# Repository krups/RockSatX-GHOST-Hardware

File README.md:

# RockSatX-GHOST-Hardware
PCB design files and documentation for the hardware used in the University of Kentucky's 2025 RockSat-XG KRUPS payload. Further information for each component is found in its respective folder.

### Hardware Folders
- [Capsule](Capsule)
- [FemtoSat](FemtoSat)
- [BaseStation/RocketStation](RocketStation)
- [LR62XE Adapter/Breakout](LR62XEAdapter)

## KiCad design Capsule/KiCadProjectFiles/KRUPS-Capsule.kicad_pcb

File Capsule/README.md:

# Capsule
PCB design files and documentation for the re-entry capsule used in the University of Kentucky's 2025 RockSat-XG KRUPS payload

### PCB Render

### Components
- [Raspberry Pi Pico 2 W (4MB Flash)](https://datasheets.raspberrypi.com/picow/pico-2-w-datasheet.pdf)
- [Fanstel LR62XE 1W 868/915MHz LoRa Modem](https://static1.squarespace.com/static/561459a2e4b0b39f5cefa12e/t/63ddc4b1dd728b424f1a6c23/1675478197953/LR62E_LR62XE_M262X840XE_Product+Specifications.pdf)
- [FSM300 9-Axis IMU](https://www.mouser.com/datasheet/2/1480/FSM30x_Datasheet-3196253.pdf)
- [H3LIS100DL 3-axis accelerometer](https://www.st.com/resource/en/datasheet/h3lis100dl.pdf)
- [MCP9600 thermocouple to digital converter](https://ww1.microchip.com/downloads/aemDocuments/documents/MSLD/ProductDocuments/DataSheets/MCP960X-L0X-RL0X-Thermocouple-EMF-to-Temperature-Converter-plus-minus-1-5-degrees-Celcius-Maximum-Accuracy-DS20005426.pdf)

### Pin Mapping
| Pico 2 GPIO Pin | Net Name |
| --- | --- |
| GPIO0 | T_IRIDIUM |
| GPIO1 | R_IRIDIUM |
| GPIO2 | SDA |
| GPIO3 | SCL |
| GPIO4 | TX1 |
| GPIO5 | RX1 |
| GPIO6 | TX_GPS |
| GPIO7 | RX_GPS |
| GPIO12 | SD_SPI_MISO |
| GPIO13 | SD_SPI_CS |
| GPIO14 | SD_SPI_CLK |
| GPIO15 | SD_SPI_MOSI |
| GPIO16 | LORA_SPI_MISO |
| GPIO17 | LORA_SPI_CSN |
| GPIO18 | LORA_SPI_CLK |
| GPIO19 | LORA_SPI_MOSI |
| GPIO20 | LORA_ANTW |
| GPIO21 | LORA_RESET |
| GPIO22 | LORA_BUSY |
| GPIO26 | LORA_DIO1 |
| GPIO27 | PWMLS |

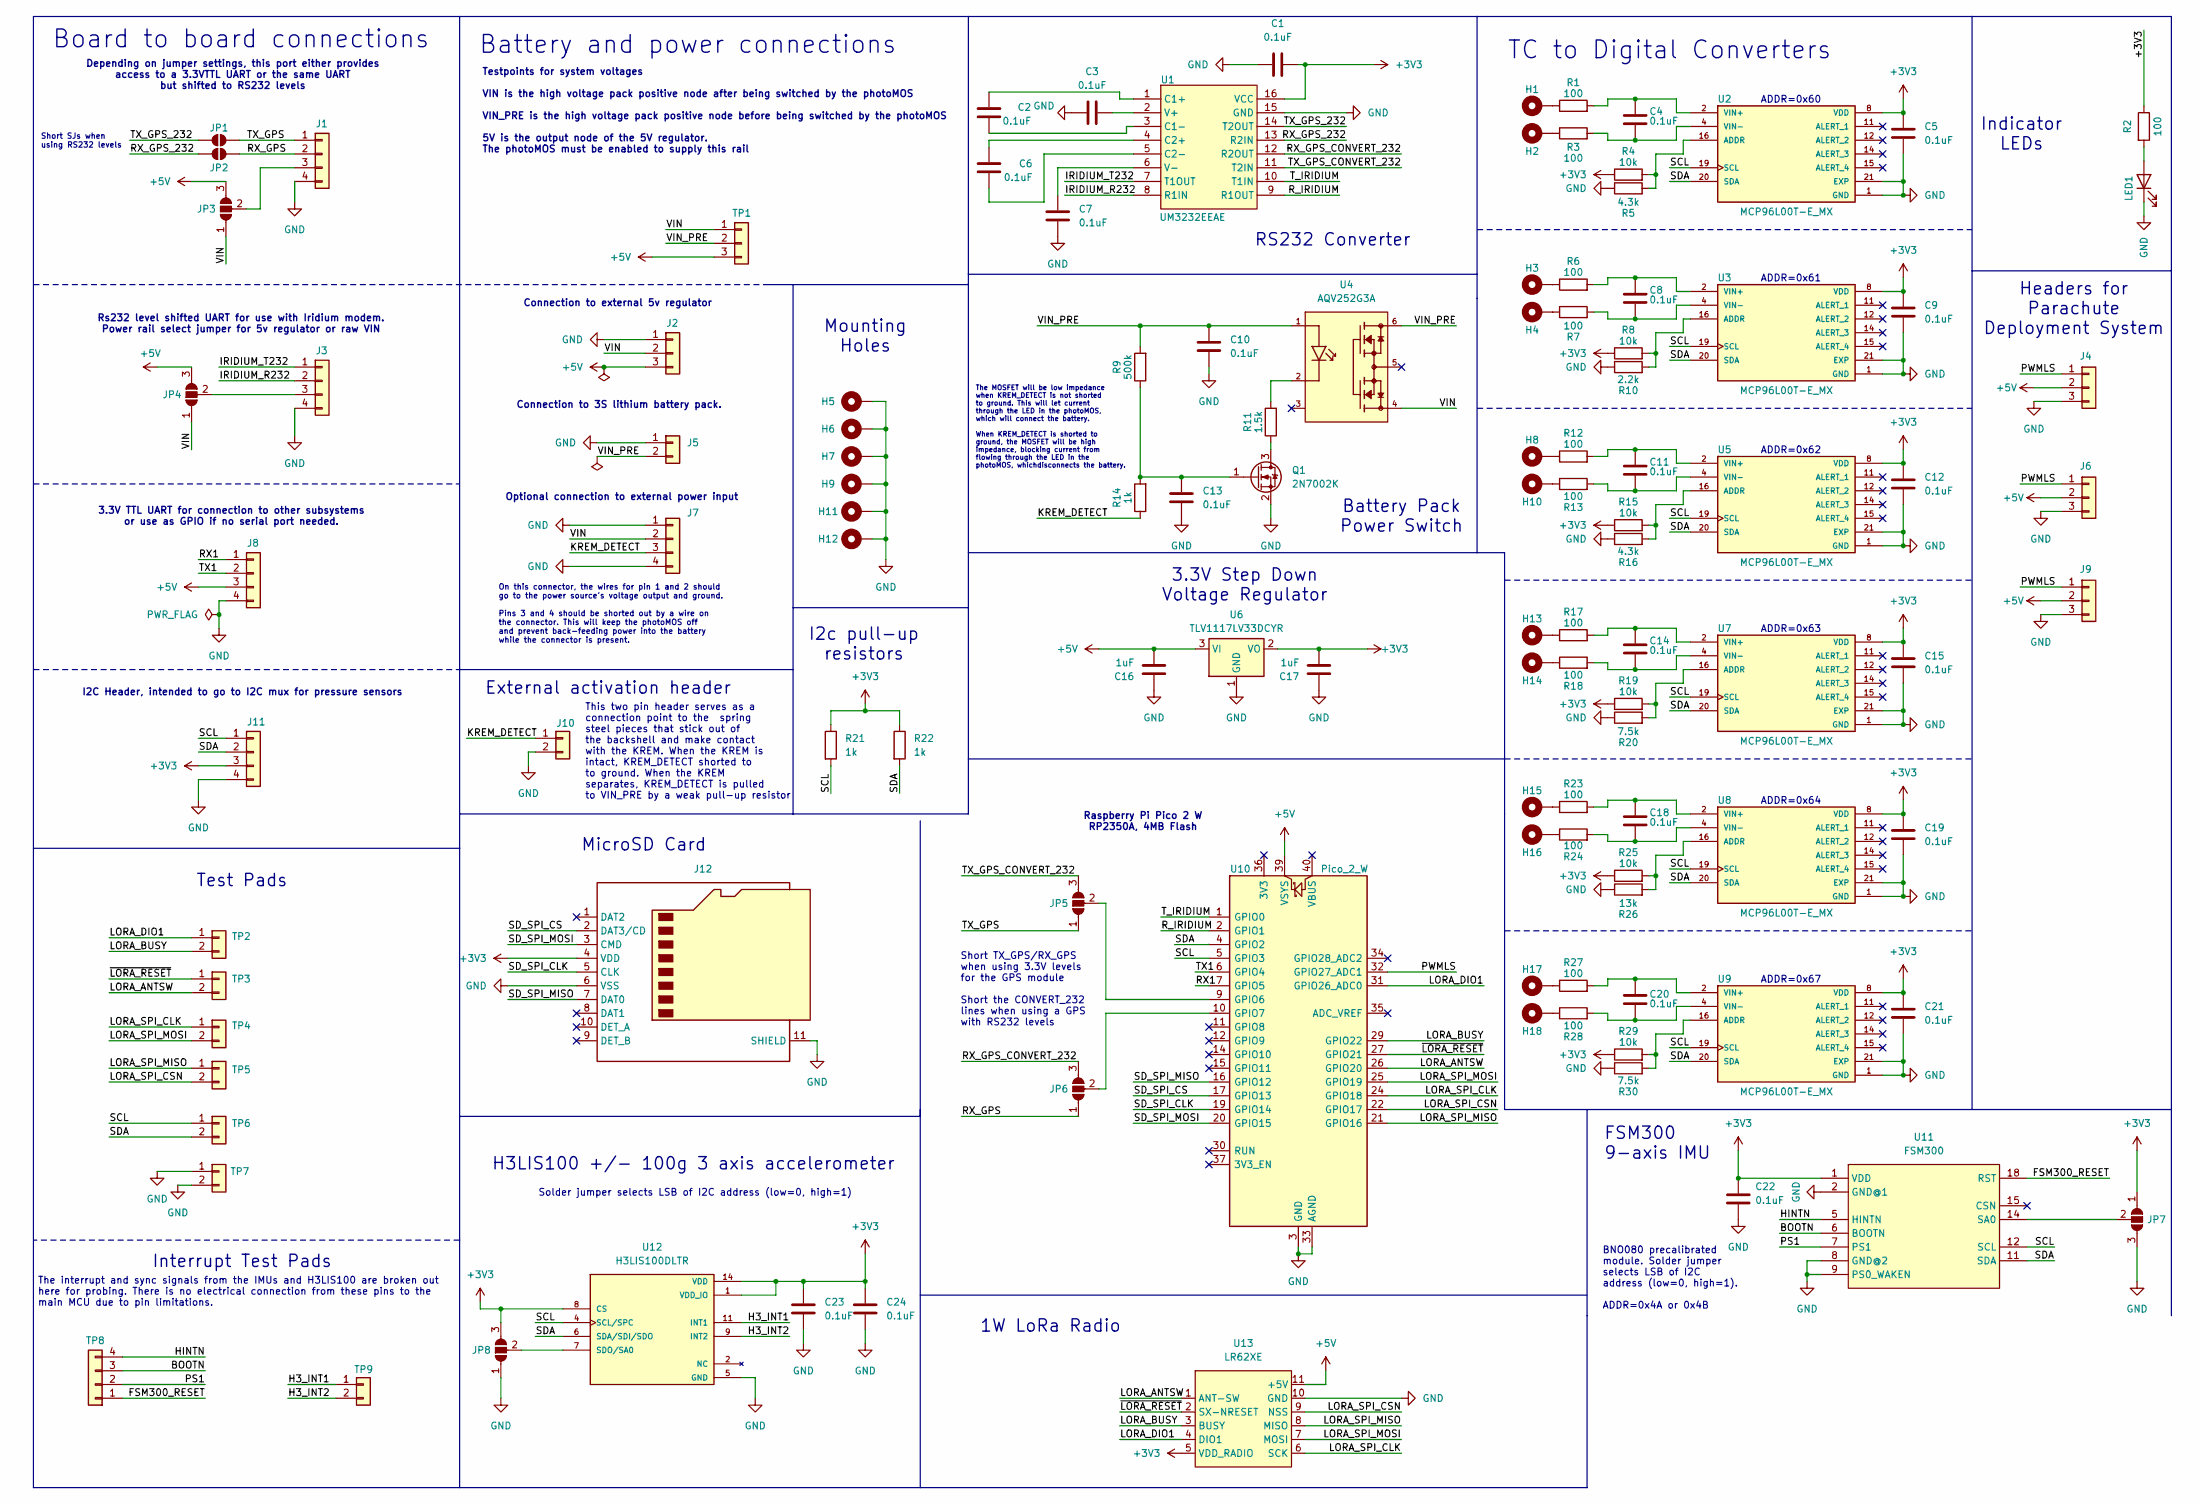
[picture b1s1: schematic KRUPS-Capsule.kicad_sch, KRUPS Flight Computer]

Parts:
C1, C2, C3, C4, C5, C6, C7, C8, C9, C10, C11, C12, C13, C14, C15, C18, C19, C20, C21, C22, C23, C24: 0.1uF; C_0603_1608Metric_Pad1.08x0.95mm_HandSolder; Digikey Part Number 0603B104K500XD
C16, C17: 1uF; C_0805_2012Metric_Pad1.18x1.45mm_HandSolder; Digikey Part Number 3372-0805B105K100CCTR-ND
H1, H2, H3, H4, H5, H6, H7, H8, H9, H10, H11, H12, H13, H14, H15, H16, H17, H18: MountingHole_Pad; 2,8-PAD
J1, J3: JST_GH_BM04B; JST_GH_BM04B-GHS-TBT_1x04-1MP_P1.25mm_Vertical; Digikey Part Number 455-BM04B-GHS-TBTTR-ND
J2: JST_VH_B4P-VH-B; JST_VH_B3P-VH-B_1x03_P3.96mm_Vertical; Digikey Part Number 455-B4P-VH-B-ND
J4, J6, J9: PinHeader_1x03_P2.54mm_Vertical; Digikey Part Number 732-5316-ND
J5: JST_VH_B2P; JST_VH_B2P-VH-B_1x02_P3.96mm_Vertical; Digikey Part Number 455-1639-ND
J7: Conn_01x04; JST_VH_B4P-VH-B_1x04_P3.96mm_Vertical; Digikey Part Number 455-B4P-VH-ND
J8: JST_GH_BM04B-GHS; JST_GH_BM04B-GHS-TBT_1x04-1MP_P1.25mm_Vertical; Digikey Part Number 455-1566-2-ND
J10: JST_GH_BM02B-GHS-TBT_1x02-1MP_P1.25mm_Vertical; Digikey Part Number 455-1564-2-ND
J11: BM04B-JST-GH; JST_GH_BM04B-GHS-TBT_1x04-1MP_P1.25mm_Vertical; Digikey Part Number 455-1566-2-ND
J12: Micro_SD_Card_Det2; microSD_HC_Molex_104031-0811; Digikey Part Number WM6357TR-ND
JP1, JP2: SolderJumper_2_Open; SolderJumper-2_P1.3mm_Open_RoundedPad1.0x1.5mm
JP3, JP4, JP5, JP6, JP7, JP8: SolderJumper_3_Open; SolderJumper-3_P1.3mm_Open_RoundedPad1.0x1.5mm_NumberLabels
LED1: LED; LED_0603_1608Metric_Pad1.05x0.95mm_HandSolder; Digikey Part Number 2679-CTL0603FYW1TTR-ND
Q1: 2N7002K; SOT-23; Digikey Part Number 2N7002KTR-ND
R1, R2, R3, R6, R7, R12, R13, R17, R18, R23, R24, R27, R28: 100; R_0603_1608Metric_Pad0.98x0.95mm_HandSolder; Digikey Part Number 311-100GRTR-ND
R4, R8, R15, R19, R25, R29: 10k; R_0603_1608Metric_Pad0.98x0.95mm_HandSolder; Digikey Part Number 13-RC0603FR-1310KLTR-ND
R5, R16: 4.3k; R_0603_1608Metric_Pad0.98x0.95mm_HandSolder; Digikey Part Number P4.30KHTR-ND
R9: 500k; R_0805_2012Metric; Digikey Part Number 738-RNCF0805BTE500KTR-ND
R10: 2.2k; R_0603_1608Metric_Pad0.98x0.95mm_HandSolder; Digikey Part Number 311-2.2KGRTR-ND
R11: 1.5k; R_0603_1608Metric_Pad0.98x0.95mm_HandSolder; Digikey Part Number 408-1766-2-ND
R14, R21, R22: 1k; R_0603_1608Metric_Pad0.98x0.95mm_HandSolder; Digikey Part Number 311-1.0KGRTR-ND
R20, R30: 7.5k; R_0603_1608Metric_Pad0.98x0.95mm_HandSolder; Digikey Part Number 311-7.5KDTR-ND
R26: 13k; R_0603_1608Metric_Pad0.98x0.95mm_HandSolder; Digikey Part Number 541-13.0KHTR-ND
TP1: Conn_01x03; PinHeader_1x03_P2.54mm_Vertical; Digikey Part Number 732-5316-ND
TP2, TP3, TP4, TP5, TP6, TP7: TEST POINT; PinHeader_1x02_P2.54mm_Vertical; Digikey Part Number 732-5315-ND
TP8: PinHeader_1x04_P2.54mm_Vertical; Digikey Part Number 732-5317-ND
TP9: Conn_01x02; PinHeader_1x02_P2.54mm_Vertical; Digikey Part Number 732-5315-ND
U1: UM3232EEAE; SSOP-16_5.3x6.2mm_P0.65mm; Digikey Part Number UM3232EEAE
U2, U3, U5, U7, U8, U9: MCP96L00T-E_MX; QFN65P500X500X100-21N_MCP96L00T-E_MX; Digikey Part Number MCP96L00T-E/MXTR-ND
U4: AQV252G3A; SMDIP-6_W7.62mm; Digikey Part Number 255-6561-ND
U6: TLV1117LV33DCYR; SOT-223-3_TabPin2; Digikey Part Number 296-28778-2-ND
U10: Pico_2_W; RaspberryPi_Pico_Common_THT; Digikey Part Number 2648-SC1633CT-ND
U11: FSM300; FSM300_FOOTPRINT; Digikey Part Number 1888-1001-ND
U12: H3LIS100DLTR; LGA-16_3x3mm_P0.5mm_LayoutBorder3x5y; Digikey Part Number 497-15697-2-ND
U13: LR62XE; Digikey Part Number 1914-LR62XETR-ND

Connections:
+3V3: C1.2, C5.1, C9.1, C12.1, C15.1, C17.1, C19.1, C21.1, C22.1, C23.1, C24.1, J11.3, J12.4 (VDD), JP7.1 (A), JP8.3 (B), R2.1, R4.1, R8.1, R15.1, R19.1, R21.1, R22.1, R25.1, R29.1, U1.16 (VCC), U2.8 (VDD), U3.8 (VDD), U5.8 (VDD), U6.2 (VO), U7.8 (VDD), U8.8 (VDD), U9.8 (VDD), U11.1 (VDD), U12.1 (VDD_IO), U12.8 (CS), U12.14 (VDD), U12.15 (VDD__1), U13.5 (VDD_RADIO)
+5V: C16.1, J2.3, J4.2, J6.2, J8.3, J9.2, JP3.3 (B), JP4.3 (B), TP1.3, U6.3 (VI), U10.39 (VSYS), U13.11 (+5V)
/BOOTN: TP8.3, U11.6 (BOOTN)
/FSM300_RESET: TP8.1, U11.18 (RST)
/H3_INT1: TP9.1, U12.11 (INT1)
/H3_INT2: TP9.2, U12.9 (INT2)
/HINTN: TP8.4, U11.5 (HINTN)
/IRIDIUM_R232: J3.2, U1.8 (R1IN)
/IRIDIUM_T232: J3.1, U1.7 (T1OUT)
/KREM_DETECT: J7.3, J10.1, R14.1
/LORA_ANTSW: TP3.2, U10.26 (GPIO20), U13.1 (ANT-SW)
/LORA_BUSY: TP2.2, U10.29 (GPIO22), U13.3 (BUSY)
/LORA_DIO1: TP2.1, U10.31 (GPIO26_ADC0), U13.4 (DIO1)
/LORA_SPI_CLK: TP4.1, U10.24 (GPIO18), U13.6 (SCK)
/LORA_SPI_CSN: TP5.2, U10.22 (GPIO17), U13.9 (NSS)
/LORA_SPI_MISO: TP5.1, U10.21 (GPIO16), U13.8 (MISO)
/LORA_SPI_MOSI: TP4.2, U10.25 (GPIO19), U13.7 (MOSI)
/PS1: TP8.2, U11.7 (PS1)
/PWMLS: J4.1, J6.1, J9.1, U10.32 (GPIO27_ADC1)
/RX1: J8.1, U10.7 (GPIO5)
/RX_GPS: J1.2, JP2.2 (B), JP6.1 (A)
/RX_GPS_232: JP2.1 (A), U1.13 (R2IN)
/RX_GPS_CONVERT_232: JP6.3 (B), U1.12 (R2OUT)
/R_IRIDIUM: U1.9 (R1OUT), U10.2 (GPIO1)
/SCL: J11.1, R21.2, TP6.1, U2.19 (SCL), U3.19 (SCL), U5.19 (SCL), U7.19 (SCL), U8.19 (SCL), U9.19 (SCL), U10.5 (GPIO3), U11.12 (SCL), U12.4 (SCL/SPC)
/SDA: J11.2, R22.2, TP6.2, U2.20 (SDA), U3.20 (SDA), U5.20 (SDA), U7.20 (SDA), U8.20 (SDA), U9.20 (SDA), U10.4 (GPIO2), U11.11 (SDA), U12.6 (SDA/SDI/SDO)
/SD_SPI_CLK: J12.5 (CLK), U10.19 (GPIO14)
/SD_SPI_CS: J12.2 (DAT3/CD), U10.17 (GPIO13)
/SD_SPI_MISO: J12.7 (DAT0), U10.16 (GPIO12)
/SD_SPI_MOSI: J12.3 (CMD), U10.20 (GPIO15)
/TX1: J8.2, U10.6 (GPIO4)
/TX_GPS: J1.1, JP1.2 (B), JP5.1 (A)
/TX_GPS_232: JP1.1 (A), U1.14 (T2OUT)
/TX_GPS_CONVERT_232: JP5.3 (B), U1.11 (T2IN)
/T_IRIDIUM: U1.10 (T1IN), U10.1 (GPIO0)
/VIN: J2.2, J7.2, JP3.1 (A), JP4.1 (A), TP1.1, U4.4
/VIN_PRE: C10.2, J5.2, R9.2, TP1.2, U4.1, U4.6
/~LORA_RESET: TP3.1, U10.27 (GPIO21), U13.2 (SX-NRESET)
GND: C1.1, C3.1, C5.2, C7.1, C9.2, C10.1, C12.2, C13.1, C15.2, C16.2, C17.2, C19.2, C21.2, C22.2, C23.2, C24.2, H5.1, H6.1, H7.1, H9.1, H11.1, H12.1, J1.4, J2.1, J3.4, J4.3, J5.1, J6.3, J7.1, J7.4, J8.4, J9.3, J10.2, J11.4, J12.6 (VSS), J12.11 (SHIELD), JP7.3 (B), JP8.1 (A), LED1.1 (K), Q1.2 (S), R5.1, R10.1, R16.1, R20.1, R26.1, R30.1, TP7.1, TP7.2, U1.15 (GND), U2.1 (GND), U2.3 (GND__1), U2.5 (GND__2), U2.6 (GND__3), U2.7 (GND__4), U2.9 (GND__5), U2.10 (GND__6), U2.13 (GND__7), U2.17 (GND__8), U2.18 (GND__9), U2.21 (EXP), U2.22 (EXP__1), U2.23 (EXP__2), U2.24 (EXP__3), U2.25 (EXP__4), U2.26 (EXP__5), U2.27 (EXP__6), U2.28 (EXP__7), U2.29 (EXP__8), U2.30 (EXP__9), U3.1 (GND), U3.3 (GND__1), U3.5 (GND__2), U3.6 (GND__3), U3.7 (GND__4), U3.9 (GND__5), U3.10 (GND__6), U3.13 (GND__7), U3.17 (GND__8), U3.18 (GND__9), U3.21 (EXP), U3.22 (EXP__1), U3.23 (EXP__2), U3.24 (EXP__3), U3.25 (EXP__4), U3.26 (EXP__5), U3.27 (EXP__6), U3.28 (EXP__7), U3.29 (EXP__8), U3.30 (EXP__9), U5.1 (GND), U5.3 (GND__1), U5.5 (GND__2), U5.6 (GND__3), U5.7 (GND__4), U5.9 (GND__5), U5.10 (GND__6), U5.13 (GND__7), U5.17 (GND__8), U5.18 (GND__9), U5.21 (EXP), U5.22 (EXP__1), U5.23 (EXP__2), U5.24 (EXP__3), U5.25 (EXP__4), U5.26 (EXP__5), U5.27 (EXP__6), U5.28 (EXP__7), U5.29 (EXP__8), U5.30 (EXP__9), U6.1 (GND), U7.1 (GND), U7.3 (GND__1), U7.5 (GND__2), U7.6 (GND__3), U7.7 (GND__4), U7.9 (GND__5), U7.10 (GND__6), U7.13 (GND__7), U7.17 (GND__8), U7.18 (GND__9), U7.21 (EXP), U7.22 (EXP__1), U7.23 (EXP__2), U7.24 (EXP__3), U7.25 (EXP__4), U7.26 (EXP__5), U7.27 (EXP__6), U7.28 (EXP__7), U7.29 (EXP__8), U7.30 (EXP__9), U8.1 (GND), U8.3 (GND__1), U8.5 (GND__2), U8.6 (GND__3), U8.7 (GND__4), U8.9 (GND__5), U8.10 (GND__6), U8.13 (GND__7), U8.17 (GND__8), U8.18 (GND__9), U8.21 (EXP), U8.22 (EXP__1), U8.23 (EXP__2), U8.24 (EXP__3), U8.25 (EXP__4), U8.26 (EXP__5), U8.27 (EXP__6), U8.28 (EXP__7), U8.29 (EXP__8), U8.30 (EXP__9), U9.1 (GND), U9.3 (GND__1), U9.5 (GND__2), U9.6 (GND__3), U9.7 (GND__4), U9.9 (GND__5), U9.10 (GND__6), U9.13 (GND__7), U9.17 (GND__8), U9.18 (GND__9), U9.21 (EXP), U9.22 (EXP__1), U9.23 (EXP__2), U9.24 (EXP__3), U9.25 (EXP__4), U9.26 (EXP__5), U9.27 (EXP__6), U9.28 (EXP__7), U9.29 (EXP__8), U9.30 (EXP__9), U10.3 (GND), U10.8 (GND), U10.13 (GND), U10.18 (GND), U10.23 (GND), U10.28 (GND), U10.33 (AGND), U10.38 (GND), U11.2 (GND@1), U11.8 (GND@2), U11.9 (PS0_WAKEN), U12.5 (GND), U12.10 (GND__1), U12.12 (GND__2), U12.13 (GND__3), U12.16 (GND__4), U13.10 (GND), U13.12 (GND)
unnamed: H1.1, R1.1
unnamed: H2.1, R3.1
unnamed: H3.1, R6.1
unnamed: H4.1, R7.1
unnamed: H8.1, R12.1
unnamed: H10.1, R13.1
unnamed: H13.1, R17.1
unnamed: H14.1, R18.1
unnamed: H15.1, R23.1
unnamed: H16.1, R24.1
unnamed: H17.1, R27.1
unnamed: H18.1, R28.1
unnamed: J1.3, JP3.2 (C)
unnamed: J3.3, JP4.2 (C)
unnamed: JP5.2 (C), U10.9 (GPIO6)
unnamed: JP6.2 (C), U10.10 (GPIO7)
unnamed: JP7.2 (C), U11.14 (SA0)
unnamed: JP8.2 (C), U12.7 (SDO/SA0)
unnamed: LED1.2 (A), R2.2
unnamed: Q1.3 (D), R11.1
unnamed: C13.2, Q1.1 (G), R9.1, R14.2
unnamed: R11.2, U4.2
unnamed: C2.2, U1.1 (C1+)
unnamed: C2.1, U1.3 (C1-)
unnamed: C6.2, U1.4 (C2+)
unnamed: C6.1, U1.5 (C2-)
unnamed: C3.2, U1.2 (V+)
unnamed: C7.2, U1.6 (V-)
unnamed: R4.2, R5.2, U2.16 (ADDR)
unnamed: C4.1, R1.2, U2.2 (VIN+)
unnamed: C4.2, R3.2, U2.4 (VIN-)
unnamed: R8.2, R10.2, U3.16 (ADDR)
unnamed: C8.1, R6.2, U3.2 (VIN+)
unnamed: C8.2, R7.2, U3.4 (VIN-)
unnamed: R15.2, R16.2, U5.16 (ADDR)
unnamed: C11.1, R12.2, U5.2 (VIN+)
unnamed: C11.2, R13.2, U5.4 (VIN-)
unnamed: R19.2, R20.2, U7.16 (ADDR)
unnamed: C14.1, R17.2, U7.2 (VIN+)
unnamed: C14.2, R18.2, U7.4 (VIN-)
unnamed: R25.2, R26.2, U8.16 (ADDR)
unnamed: C18.1, R23.2, U8.2 (VIN+)
unnamed: C18.2, R24.2, U8.4 (VIN-)
unnamed: R29.2, R30.2, U9.16 (ADDR)
unnamed: C20.1, R27.2, U9.2 (VIN+)
unnamed: C20.2, R28.2, U9.4 (VIN-)

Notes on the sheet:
Indicator LEDs
Test Pads
Short TX_GPS/RX_GPS when using 3.3V levels for the GPS module Short the CONVERT_232 lines when using a GPS with RS232 levels
ADDR=0x67
I2C Header, intended to go to I2C mux for pressure sensors
ADDR=0x63
I2c pull-up resistors
Rs232 level shifted UART for use with Iridium modem. Power rail select jumper for 5v regulator or raw VIN
RS232 Converter
This two pin header serves as a connection point to the spring steel pieces that stick out of the backshell and make contact with the KREM. When the KREM is intact, KREM_DETECT shorted to to ground. When the KREM separates, KREM_DETECT is pulled to VIN_PRE by a weak pull-up resistor
The interrupt and sync signals from the IMUs and H3LIS100 are broken out here for probing. There is no electrical connection from these pins to the main MCU due to pin limitations.
External activation header
ADDR=0x62
FSM300 9-axis IMU
Mounting Holes
Optional connection to external power input
1W LoRa Radio
Testpoints for system voltages VIN is the high voltage pack positive node after being switched by the photoMOS VIN_PRE is the high voltage pack positive node before being switched by the photoMOS 5V is the output node of the 5V regulator. The photoMOS must be enabled to supply this rail
Board to board connections
Depending on jumper settings, this port either provides access to a 3.3VTTL UART or the same UART but shifted to RS232 levels
BNO080 precalibrated module. Solder jumper selects LSB of I2C address (low=0, high=1). ADDR=0x4A or 0x4B
ADDR=0x64
H3LIS100 +/- 100g 3 axis accelerometer
3.3V TTL UART for connection to other subsystems or use as GPIO if no serial port needed.
ADDR=0x61
Headers for Parachute Deployment System
Short SJs when using RS232 levels
Raspberry Pi Pico 2 W RP2350A, 4MB Flash
On this connector, the wires for pin 1 and 2 should go to the power source's voltage output and ground. Pins 3 and 4 should be shorted out by a wire on the connector. This will keep the photoMOS off and prevent back-feeding power into the battery while the connector is present.
3.3V Step Down Voltage Regulator
Interrupt Test Pads
The MOSFET will be low impedance when KREM_DETECT is not shorted to ground. This will let current through the LED in the photoMOS, which will connect the battery. When KREM_DETECT is shorted to ground, the MOSFET will be high impedance, blocking current from flowing through the LED in the photoMOS,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
Solder jumper selects LSB of I2C address (low=0, high=1)
Connection to 3S lithium battery pack.
TC to Digital Converters
Battery Pack Power Switch
Battery and power connections
Connection to external 5v regulator
MicroSD Card
ADDR=0x60

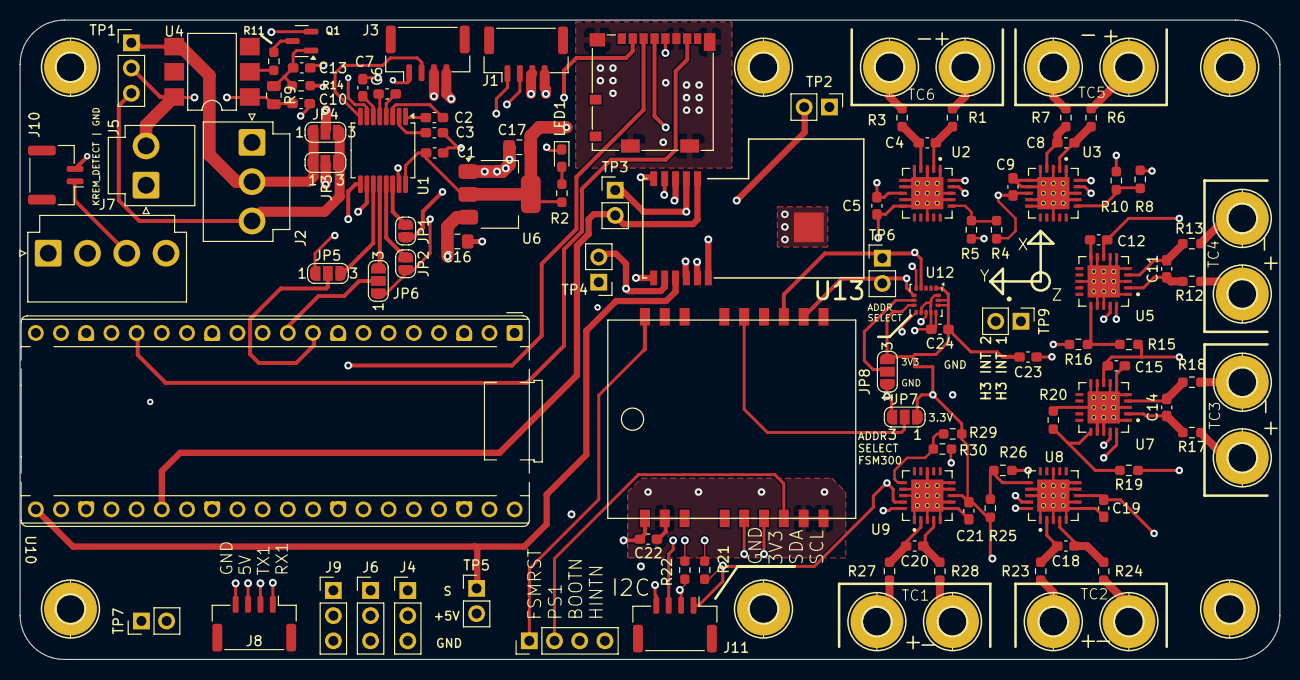
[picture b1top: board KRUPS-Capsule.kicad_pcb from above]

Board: 6 copper layers, 127.0 x 64.4 mm, 116 parts (0 on the bottom side), 85 nets.

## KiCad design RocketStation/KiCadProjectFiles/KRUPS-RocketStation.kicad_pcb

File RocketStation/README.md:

# KRUPS-RocketStation
PCB design files and documentation for the base station/rocket station used in the University of Kentucky's 2025 RockSat-XG KRUPS payload

### PCB Render

### Components
- [Raspberry Pi Pico 2 W (4MB Flash)](https://datasheets.raspberrypi.com/picow/pico-2-w-datasheet.pdf)
- [Fanstel LR62XE 1W 868/915MHz LoRa Modem](https://static1.squarespace.com/static/561459a2e4b0b39f5cefa12e/t/63ddc4b1dd728b424f1a6c23/1675478197953/LR62E_LR62XE_M262X840XE_Product+Specifications.pdf)
- [BME280 Temperature, Pressure, Humidity Sensor](https://www.bosch-sensortec.com/media/boschsensortec/downloads/datasheets/bst-bme280-ds002.pdf)
- [BNO086 9-Axis IMU](https://www.mouser.com/datasheet/2/1480/BNO080_085_Datasheet-3196201.pdf)
- [PKU5511ESI DC/DC Step-down Converter](https://flexpowermodules.com/resources/fpm-techspec-pku5500e)

### Pin Mapping
| Pico 2 W GPIO Pin | Net Name |
| --- | --- |
| GPIO0 | RPI_UART4_TX |
| GPIO1 | RPI_UART4_RX |
| GPIO4 | ASYNC_UART_TX1 |
| GPIO5 | ASYNC_UART_TX2 |
| GPIO6 | SPI_CLK |
| GPIO7 | SPI_MOSI |
| GPIO8 | SPI_MISO |
| GPIO9 | SPI_NSS |
| GPIO10 | LORA_DIO1 |
| GPIO11 | LORA_BUSY |
| GPIO12 | LORA_RESET (active low)|
| GPIO13 | LORA_ANTSW |
| GPIO14 | I2C_SDA |
| GPIO15 | I2C_SCL |
| GPIO19 | BNO086_RESET (active low) |
| GPIO20 | BNO086_HINTN |
| GPIO26 | TE_SENSE (ADC) |

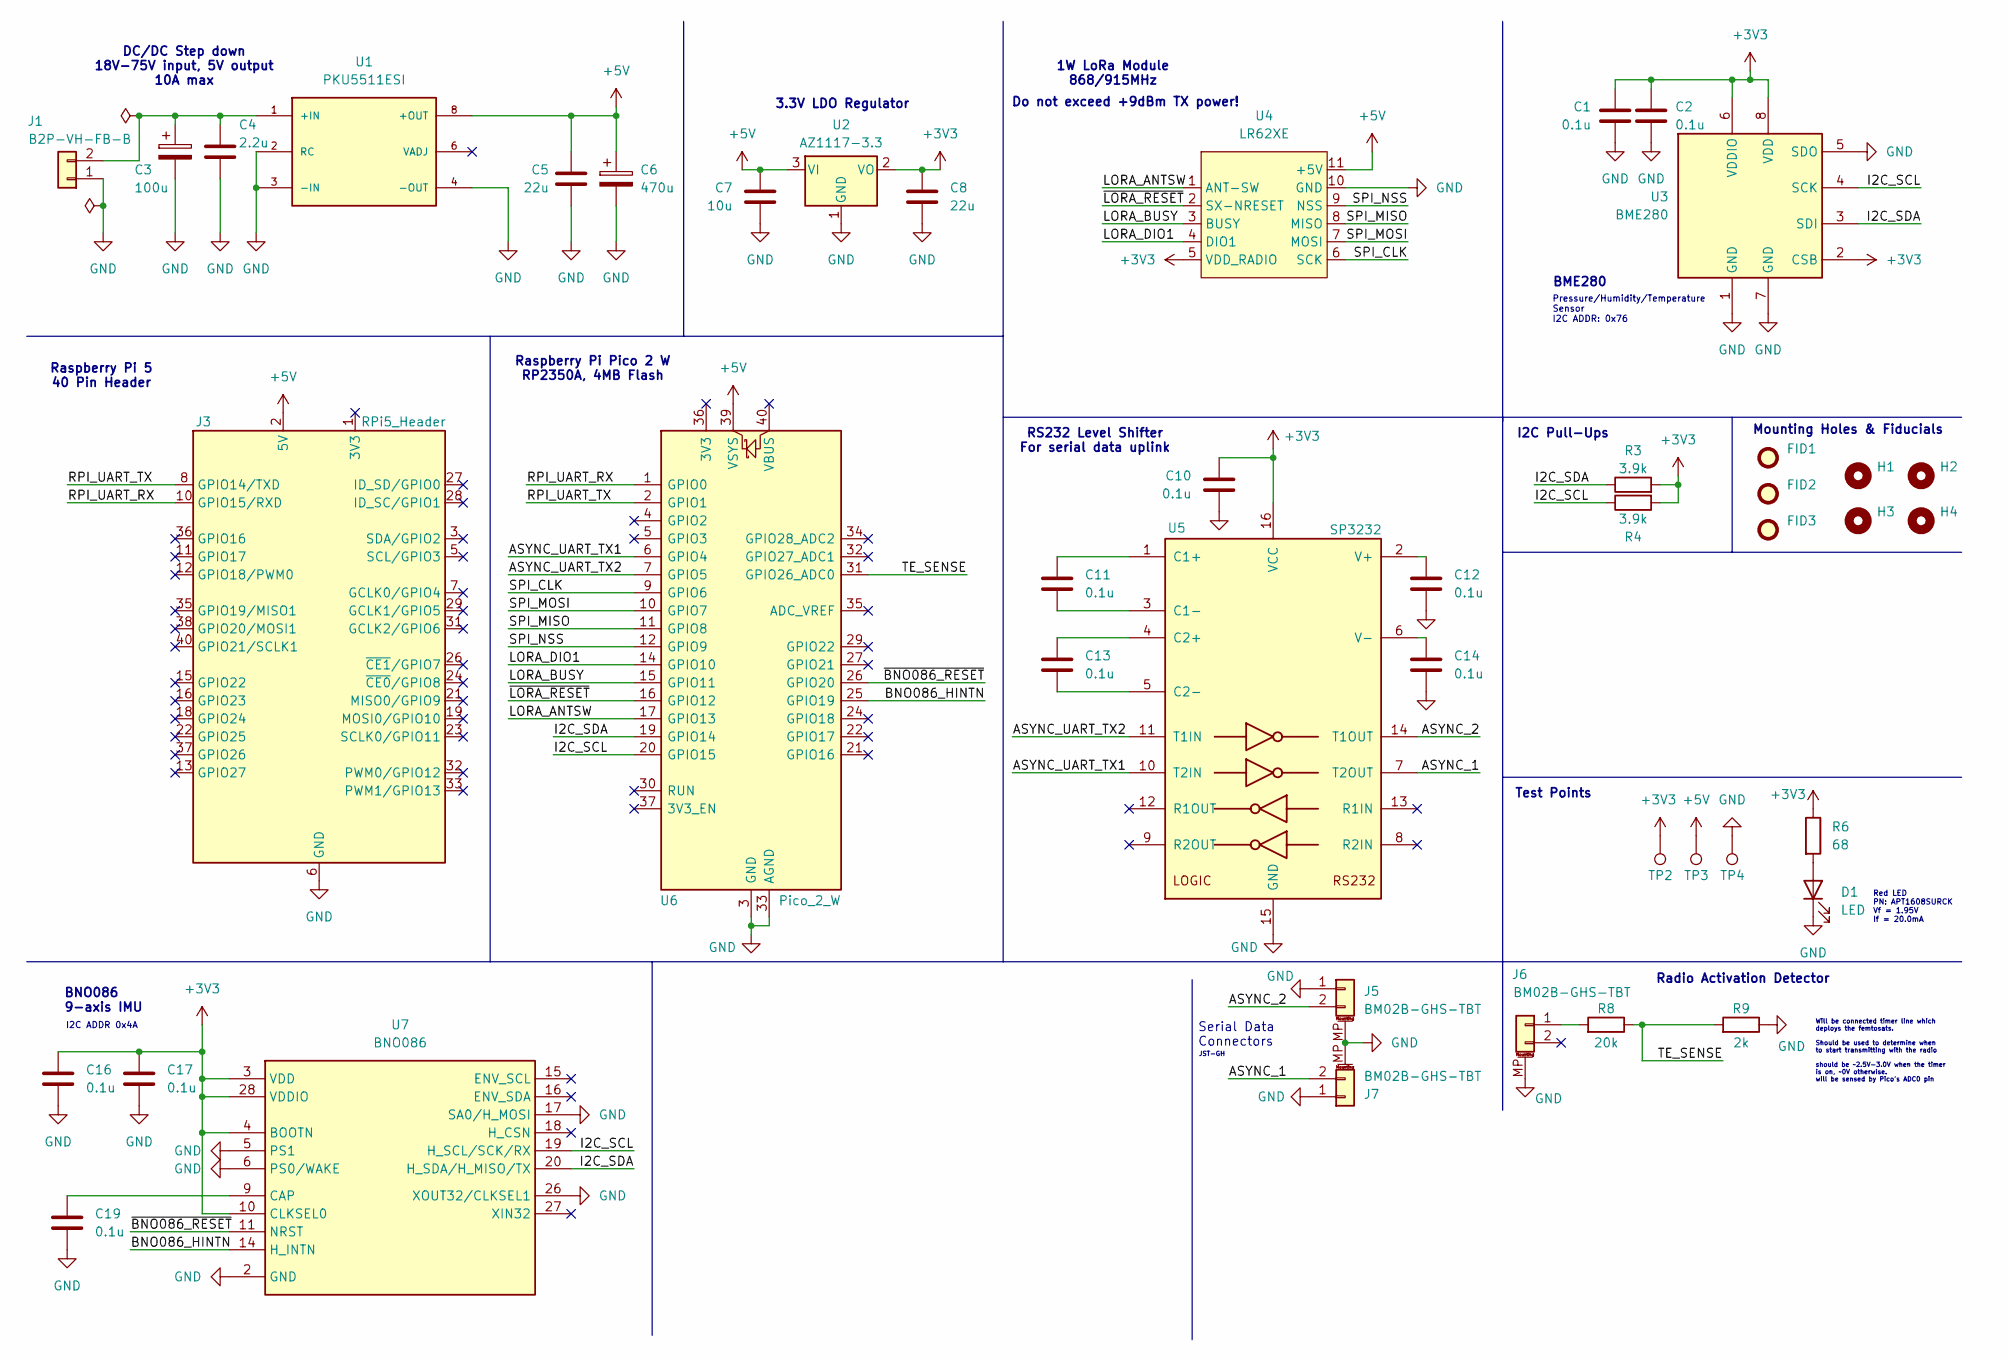
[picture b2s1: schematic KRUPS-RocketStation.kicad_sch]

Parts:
C1, C2, C10, C11, C12, C13, C14, C16, C17, C19: 0.1u; C_0603_1608Metric_Pad1.08x0.95mm_HandSolder; Digikey Part Number CC0603KRX7R7BB104
C3: 100u; A768MS_Anti_Vibration; Digikey Part Number A768MS107M1JLAV027
C4: 2.2u; C_1206_3216Metric_Pad1.33x1.80mm_HandSolder; Digikey Part Number 12061C225KAT2A
C5, C8: 22u; C_0805_2012Metric_Pad1.18x1.45mm_HandSolder; Digikey Part Number CL21A226MPQNNNE
C6: 470u; A768MS_Anti_Vibration; Digikey Part Number A768MS477M1ELAV017
C7: 10u; C_0805_2012Metric_Pad1.18x1.45mm_HandSolder; Digikey Part Number CL21A106KOQNNNG
D1: LED; D_0603_1608Metric_Pad1.05x0.95mm_HandSolder; Digikey Part Number APT1608SURCK
FID1, FID2, FID3: Fiducial; Fiducial_0.75mm_Mask1.5mm
H1: MountingHole; MountingHole_2.7mm_M2.5
H2, H3, H4: MountingHole; MountingHole_2.7mm_M2.5_Pad
J1: B2P-VH-FB-B; JST_VH_B2P-VH-FB-B_1x02_P3.96mm_Vertical; Digikey Part Number B2P-VH-FB-B
J3: RPi5_Header; PinSocket_2x20_P2.54mm_Vertical; Digikey Part Number PRT-16764
J5, J6, J7: BM02B-GHS-TBT; JST_GH_BM02B-GHS-TBT_1x02-1MP_P1.25mm_Vertical; Digikey Part Number BM02B-GHS-TBT
R3, R4: 3.9k; R_0603_1608Metric_Pad0.98x0.95mm_HandSolder; Digikey Part Number ERJ-3EKF3901V
R6: 68; R_0603_1608Metric_Pad0.98x0.95mm_HandSolder; Digikey Part Number RC0603JR-0768RL
R8: 20k; R_0603_1608Metric_Pad0.98x0.95mm_HandSolder; Digikey Part Number ERJ-3EKF2002V
R9: 2k; R_0603_1608Metric_Pad0.98x0.95mm_HandSolder; Digikey Part Number ERJ-3EKF2001V
TP2, TP3, TP4: TestPoint; PinHeader_1x01_P2.54mm_Vertical
U1: PKU5511ESI; CONV_PKU5511ESI; Digikey Part Number PKU5511ESI
U2: AZ1117-3.3; SOT-89-3_Handsoldering; Digikey Part Number AZ1117CR2-3.3TRG1
U3: BME280; Bosch_LGA-8_2.5x2.5mm_P0.65mm_ClockwisePinNumbering; Digikey Part Number BME280
U4: LR62XE
U5: SP3232; TSSOP-16_4.4x5mm_P0.65mm; Digikey Part Number SP3232EUEY-L/TR
U6: Pico_2_W; RaspberryPi_Pico_Common_THT
U7: BNO086; LGA-28_5.2x3.8mm_P0.5mm; Manufacturer_Part_Number BNO086; Mouser Part Number 526-BNO086

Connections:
+3V3: C1.1, C2.1, C8.1, C10.1, C16.1, C17.1, R3.2, R4.2, R6.1, TP2.1, U2.2 (VO), U3.2 (CSB), U3.6 (VDDIO), U3.8 (VDD), U4.5 (VDD_RADIO), U5.16 (VCC), U7.3 (VDD), U7.4 (BOOTN), U7.10 (CLKSEL0), U7.28 (VDDIO)
+5V: C5.1, C6.1, C7.1, J3.2 (5V), J3.4 (5V), TP3.1, U1.8 (+OUT), U2.3 (VI), U4.11 (+5V), U6.39 (VSYS)
/ASYNC_1: J7.2, U5.7 (T2OUT)
/ASYNC_2: J5.2, U5.14 (T1OUT)
/ASYNC_UART_TX1: U5.10 (T2IN), U6.6 (GPIO4)
/ASYNC_UART_TX2: U5.11 (T1IN), U6.7 (GPIO5)
/BNO086_HINTN: U6.25 (GPIO19), U7.14 (H_INTN)
/I2C_SCL: R4.1, U3.4 (SCK), U6.20 (GPIO15), U7.19 (H_SCL/SCK/RX)
/I2C_SDA: R3.1, U3.3 (SDI), U6.19 (GPIO14), U7.20 (H_SDA/H_MISO/TX)
/LORA_ANTSW: U4.1 (ANT-SW), U6.17 (GPIO13)
/LORA_BUSY: U4.3 (BUSY), U6.15 (GPIO11)
/LORA_DIO1: U4.4 (DIO1), U6.14 (GPIO10)
/RPI_UART_RX: J3.10 (GPIO15/RXD), U6.1 (GPIO0)
/RPI_UART_TX: J3.8 (GPIO14/TXD), U6.2 (GPIO1)
/SPI_CLK: U4.6 (SCK), U6.9 (GPIO6)
/SPI_MISO: U4.8 (MISO), U6.11 (GPIO8)
/SPI_MOSI: U4.7 (MOSI), U6.10 (GPIO7)
/SPI_NSS: U4.9 (NSS), U6.12 (GPIO9)
/TE_SENSE: R8.1, R9.2, U6.31 (GPIO26_ADC0)
/~BNO086_RESET: U6.26 (GPIO20), U7.11 (NRST)
/~LORA_RESET: U4.2 (SX-NRESET), U6.16 (GPIO12)
GND: C1.2, C2.2, C3.2, C4.2, C5.2, C6.2, C7.2, C8.2, C10.2, C12.2, C14.2, C16.2, C17.2, C19.2, D1.1 (K), J1.1, J3.6 (GND), J3.9 (GND), J3.14 (GND), J3.20 (GND), J3.25 (GND), J3.30 (GND), J3.34 (GND), J3.39 (GND), J5.1, J5.MP (MountPin), J6.MP (MountPin), J7.1, J7.MP (MountPin), R9.1, TP4.1, U1.2 (RC), U1.3 (-IN), U1.4 (-OUT), U2.1 (GND), U3.1 (GND), U3.5 (SDO), U3.7 (GND), U4.10 (GND), U4.12 (GND), U5.15 (GND), U6.3 (GND), U6.8 (GND), U6.13 (GND), U6.18 (GND), U6.23 (GND), U6.28 (GND), U6.33 (AGND), U6.38 (GND), U7.2 (GND), U7.5 (PS1), U7.6 (PS0/WAKE), U7.17 (SA0/H_MOSI), U7.25 (GND), U7.26 (XOUT32/CLKSEL1)
unnamed: D1.2 (A), R6.2
unnamed: C3.1, C4.1, J1.2, U1.1 (+IN)
unnamed: J6.1, R8.2
unnamed: C11.1, U5.1 (C1+)
unnamed: C11.2, U5.3 (C1-)
unnamed: C13.1, U5.4 (C2+)
unnamed: C13.2, U5.5 (C2-)
unnamed: C12.1, U5.2 (V+)
unnamed: C14.1, U5.6 (V-)
unnamed: C19.1, U7.9 (CAP)

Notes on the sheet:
Pressure/Humidity/Temperature Sensor I2C ADDR: 0x76
1W LoRa Module 868/915MHz
RS232 Level Shifter For serial data uplink
3.3V LDO Regulator
I2C Pull-Ups
Red LED PN: APT1608SURCK Vf = 1.95V If = 20.0mA
Test Points
Radio Activation Detector
Serial Data Connectors
Do not exceed +9dBm TX power!
Mounting Holes & Fiducials
I2C ADDR 0x4A
Raspberry Pi 5 40 Pin Header
BME280
DC/DC Step down 18V-75V input, 5V output 10A max
BNO086 9-axis IMU
Will be connected timer line which deploys the femtosats. Should be used to determine when to start transmitting with the radio should be ~2.5V-3.0V when the timer is on, ~0V otherwise. will be sensed by Pico's ADC0 pin
Raspberry Pi Pico 2 W RP2350A, 4MB Flash
JST-GH

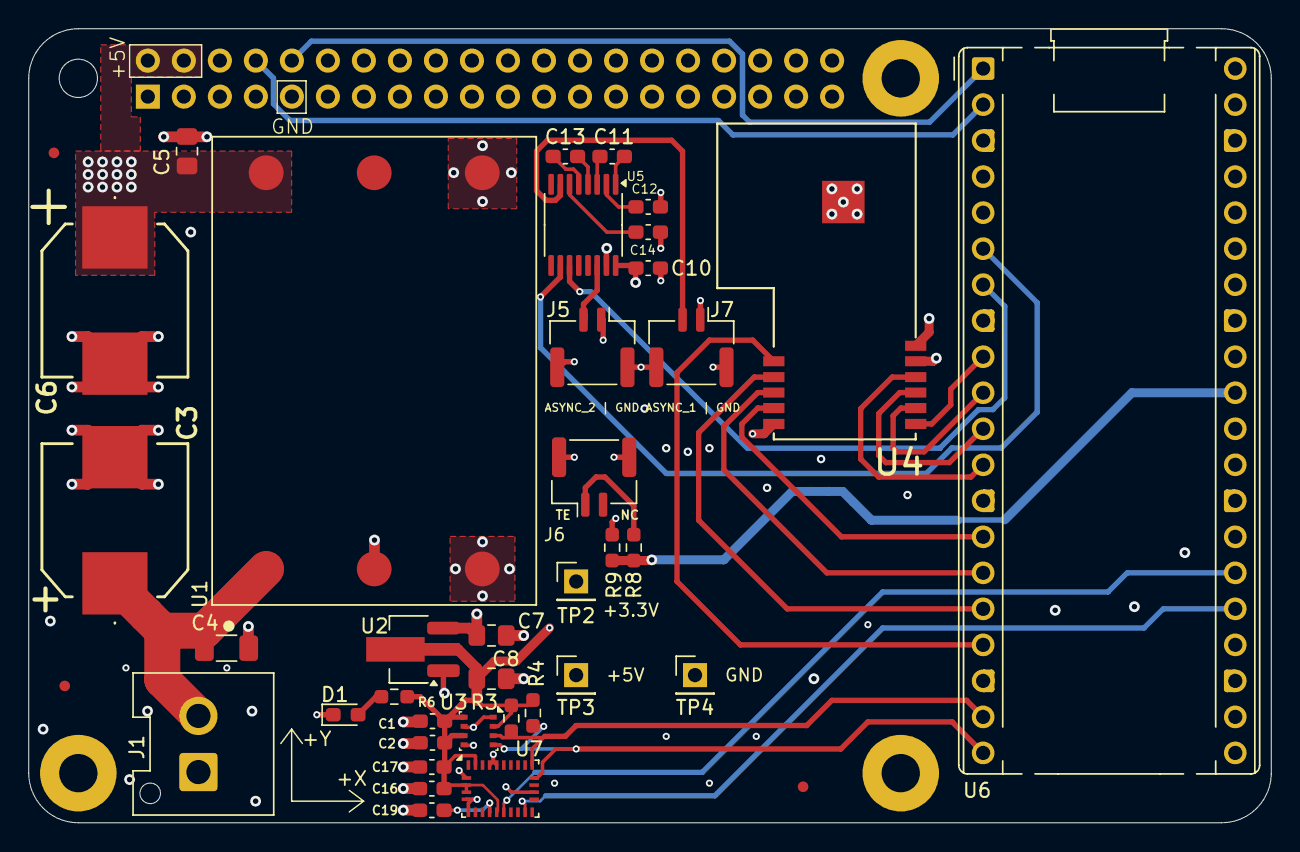
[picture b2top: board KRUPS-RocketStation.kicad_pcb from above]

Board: 4 copper layers, 87.6 x 56.0 mm, 44 parts (1 on the bottom side), 32 nets.

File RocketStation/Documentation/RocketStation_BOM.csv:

"Reference","Value","Description","Qty","DNP","Digikey Part Number"
"C1,C2,C10,C11,C12,C13,C14,C16,C17,C19","0.1u","0.1uF, 16V, X7R, SMD 0603","10","","CC0603KRX7R7BB104"
"C3","100u","100uF, 63V, Aluminum Electrolytic, SMD","1","","A768MS107M1JLAV027"
"C4","2.2u","2.2uF, 100V, X7R, SMD 1206","1","","12061C225KAT2A"
"C5,C8","22u","22uF, 10V, X5R, SMD 0805","2","","CL21A226MPQNNNE"
"C6","470u","470uF, 25V, Aluminum Electrolytic, SMD","1","","A768MS477M1ELAV017"
"C7","10u","10uF, 16V, X5R, SMD 0805","1","","CL21A106KOQNNNG"
"D1","LED","LED, 1.95V Vf, 20mA If, SMD 0603","1","","APT1608SURCK"
"J1","B2P-VH-FB-B","JST-VH 2 Pin Connector, Shielded, Vertical","1","","B2P-VH-FB-B"
"J3","RPi5_Header","Expansion header for Raspberry Pi 5","1","","PRT-16764"
"J5,J6,J7","BM02B-GHS-TBT","JST-GH 2 Pin Connector, Vertical","3","","BM02B-GHS-TBT"
"R3,R4","3.9k","3.9K OHM, 1%, 1/10W, SMD 0603","2","","ERJ-3EKF3901V"
"R6","68","68 OHM, 5%, 1/10W, SMD 0603","1","","RC0603JR-0768RL"
"R8","20k","20K OHM, 1%, 1/10W, SMD 0603","1","","ERJ-3EKF2002V"
"R9","2k","2K OHM, 1%, 1/10W, SMD 0603","1","","ERJ-3EKF2001V"
"U1","PKU5511ESI","DC/DC Step Down, 1/16 brick","1","","PKU5511ESI"
"U2","AZ1117-3.3","1A 20V Fixed LDO Linear Regulator, 3.3V, SOT-89/SOT-223/TO-220/TO-252/TO-263","1","","AZ1117CR2-3.3TRG1"
"U3","BME280","3-in-1 sensor, humidity, pressure, temperature, I2C and SPI interface, 1.71-3.6V, LGA-8","1","","BME280"
"U4","LR62XE","","1","",""
"U5","SP3232","SP3232 RS-232 Level Shifter, TSSOP-16","1","","SP3232EUEY-L/TR"
"U6","Pico_2_W","Versatile and inexpensive microcontroller module powered by an RP2350 dual-core processor","1","",""
"U7","BNO086","Accelerometer, Gyroscope, Magnetometer, Temperature, 9 Axis Sensor IC, SPI Output","1","","BNO086"
